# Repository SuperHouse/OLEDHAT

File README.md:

OLED / Voltage Regulator Hat for Raspberry Pi
==============================================
Copyright 2019 SuperHouse Automation Pty Ltd www.superhouse.tv  

FEATURES
--------

 * 128x64 1.3" OLED with I2C interface.
 * Menu buttons with I2C interface using MCP23017.
 * Supply power via 2.1mm DC jack or the PoE header on Raspberry Pi 3
   B+/4. Regulates down to 5V to supply the Raspberry Pi.

INSTALLATION
------------
The design is saved as an EAGLE project. EAGLE PCB design software is
available from www.cadsoftusa.com free for non-commercial use. To use
this project download it and place the directory containing these files
into the "eagle" directory on your computer. Then open EAGLE and
navigate to the project.

CREDITS
-------
Designed by Jonathan Oxer <jon@oxer.com.au>

DISTRIBUTION
------------
The specific terms of distribution of this project are governed by the
license referenced below.

LICENSE
-------
Licensed under the TAPR Open Hardware License (www.tapr.org/OHL).
The "license" folder within this repository also contains a copy of
this license in plain text format.

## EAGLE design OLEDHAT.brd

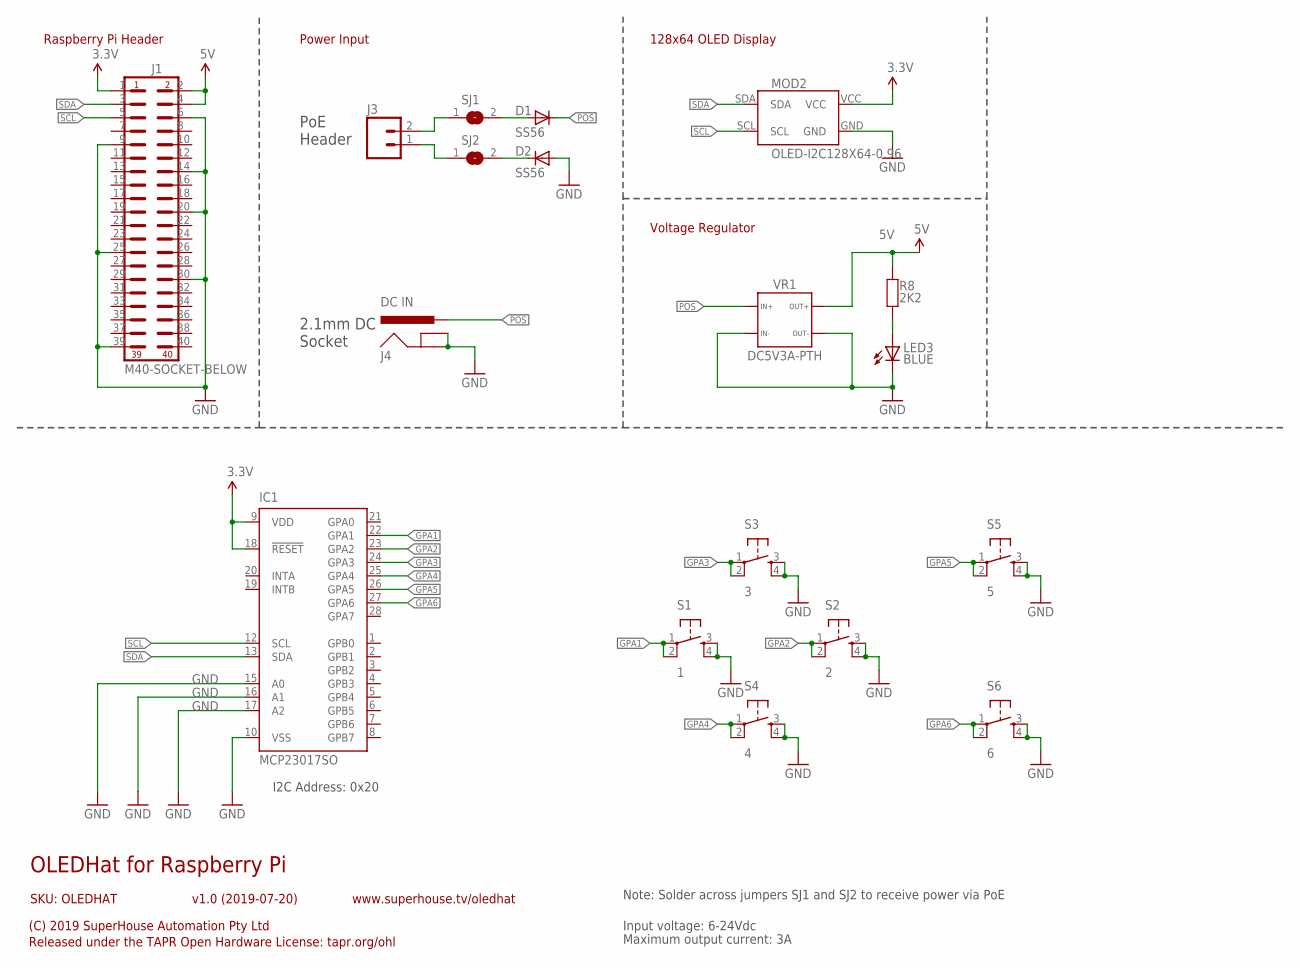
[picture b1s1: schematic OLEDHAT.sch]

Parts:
D1, D2: SS56; SMA-DIODE
IC1: MCP23017SO; SO28W
J1: M40-SOCKET-BELOW; 2X20-S-BELOW
J3: M02-SOCKET-BELOW; 1X02-S-BELOW
J4: DC IN; POWER_JACK_SLOTS
LED3: BLUE; LED-0603
MOD2: OLED-I2C128X64-0.96; OLED-128X64-0.96
R8: 2K2; R0603
S1: 1; TACTILE-PTH-4.5MM
S2: 2; TACTILE-PTH-4.5MM
S3: 3; TACTILE-PTH-4.5MM
S4: 4; TACTILE-PTH-4.5MM
S5: 5; TACTILE-PTH-4.5MM
S6: 6; TACTILE-PTH-4.5MM
SJ1, SJ2: SJN; SJ
VR1: DC5V3A-PTH

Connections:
3.3V: IC1.9 (VDD), IC1.18 (!RESET), J1.1, MOD2.VCC
5V: J1.2, J1.4, R8.1, VR1.3A (3), VR1.3B (3)
GND: D2.A, IC1.10 (VSS), IC1.15 (A0), IC1.16 (A1), IC1.17 (A2), J1.6, J1.9, J1.14, J1.20, J1.25, J1.30, J1.39, J4.GND, J4.GNDBREAK, LED3.C, MOD2.GND, S1.3, S1.4, S2.3, S2.4, S3.3, S3.4, S4.3, S4.4, S5.3, S5.4, S6.3, S6.4, VR1.1A (1), VR1.1B (1), VR1.4A (4), VR1.4B (4)
GPA1: IC1.22 (GPA1), S1.1, S1.2
GPA2: IC1.23 (GPA2), S2.1, S2.2
GPA3: IC1.24 (GPA3), S3.1, S3.2
GPA4: IC1.25 (GPA4), S4.1, S4.2
GPA5: IC1.26 (GPA5), S5.1, S5.2
GPA6: IC1.27 (GPA6), S6.1, S6.2
unnamed: J3.1, SJ2.1
unnamed: J3.2, SJ1.1
unnamed: D1.A, SJ1.2
unnamed: D2.C, SJ2.2
unnamed: LED3.A, R8.2
POS: D1.C, J4.PWR, VR1.2A (2), VR1.2B (2)
SCL: IC1.12 (SCL), J1.5, MOD2.SCL
SDA: IC1.13 (SDA), J1.3, MOD2.SDA

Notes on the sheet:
OLEDHat for Raspberry Pi
v1.0 (2019-07-20)
(C) 2019 SuperHouse Automation Pty Ltd
Released under the TAPR Open Hardware License: tapr.org/ohl
www.superhouse.tv/oledhat
SKU: OLEDHAT
Raspberry Pi Header
Input voltage: 6-24Vdc
Maximum output current: 3A
PoE Header
2.1mm DC Socket
Power Input
128x64 OLED Display
Voltage Regulator
Note: Solder across jumpers SJ1 and SJ2 to receive power via PoE
I2C Address: 0x20

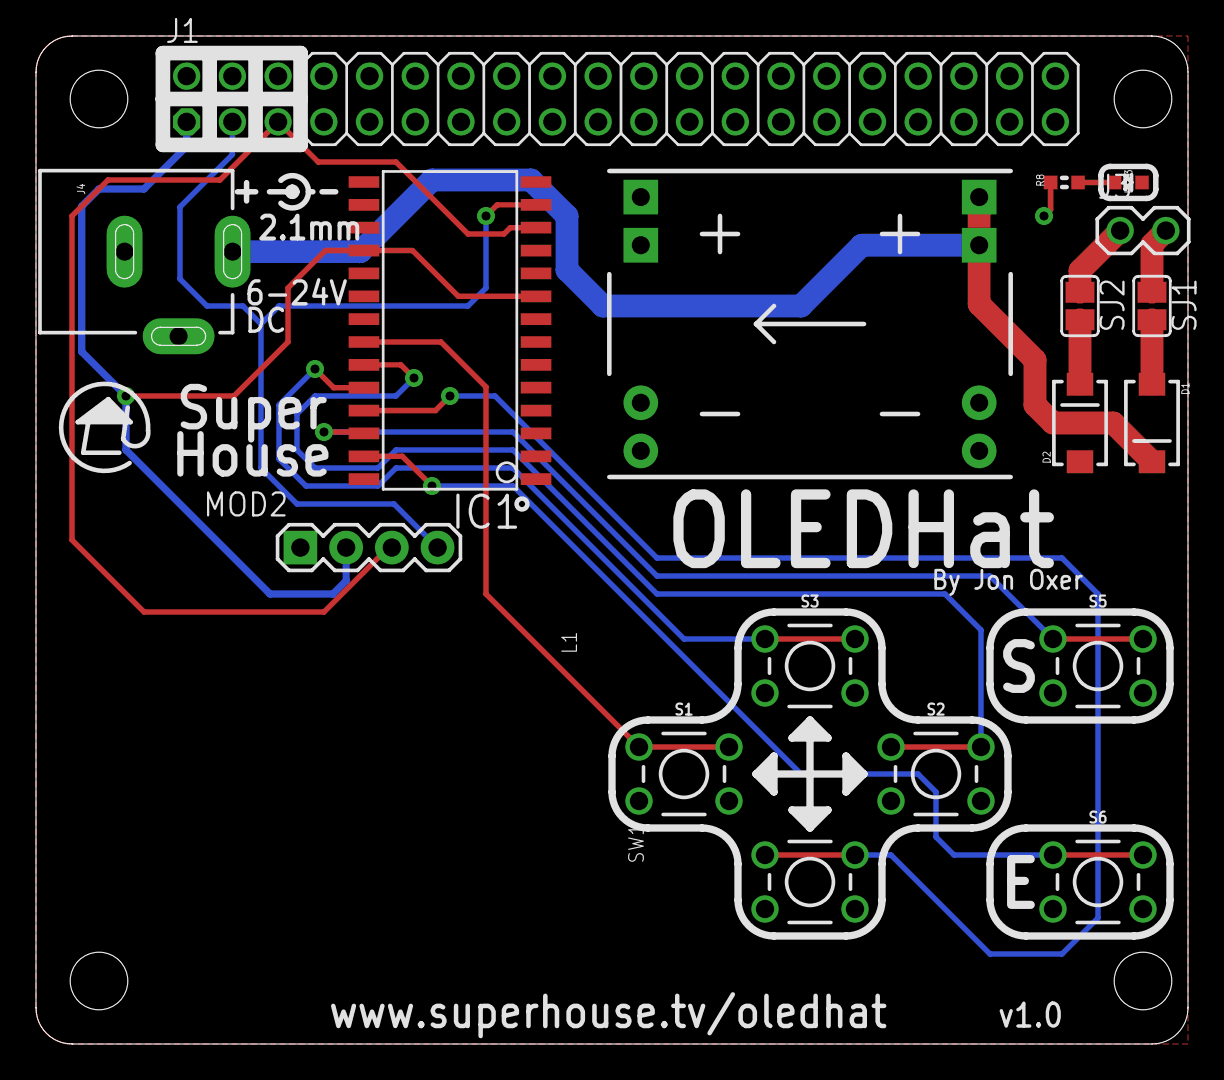
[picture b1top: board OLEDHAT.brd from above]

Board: 2 copper layers, 64.0 x 56.0 mm, 18 parts (0 on the bottom side), 17 nets.

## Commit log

2019-09-02 Migrated project files
2019-09-02 Adapted README for this project
2019-09-13 Final routing, plus ERC and DRC for v1.0 release
